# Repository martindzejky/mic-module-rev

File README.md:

# Microphone module reverse-engineered

I had this microphone sensor module lying around. I wanted to understand how it works
so I reverse engineered its schematic. I also ended up re-creating the PCB and a 3D model.

Everything was done in [KiCad](https://www.kicad-pcb.org).

## Images

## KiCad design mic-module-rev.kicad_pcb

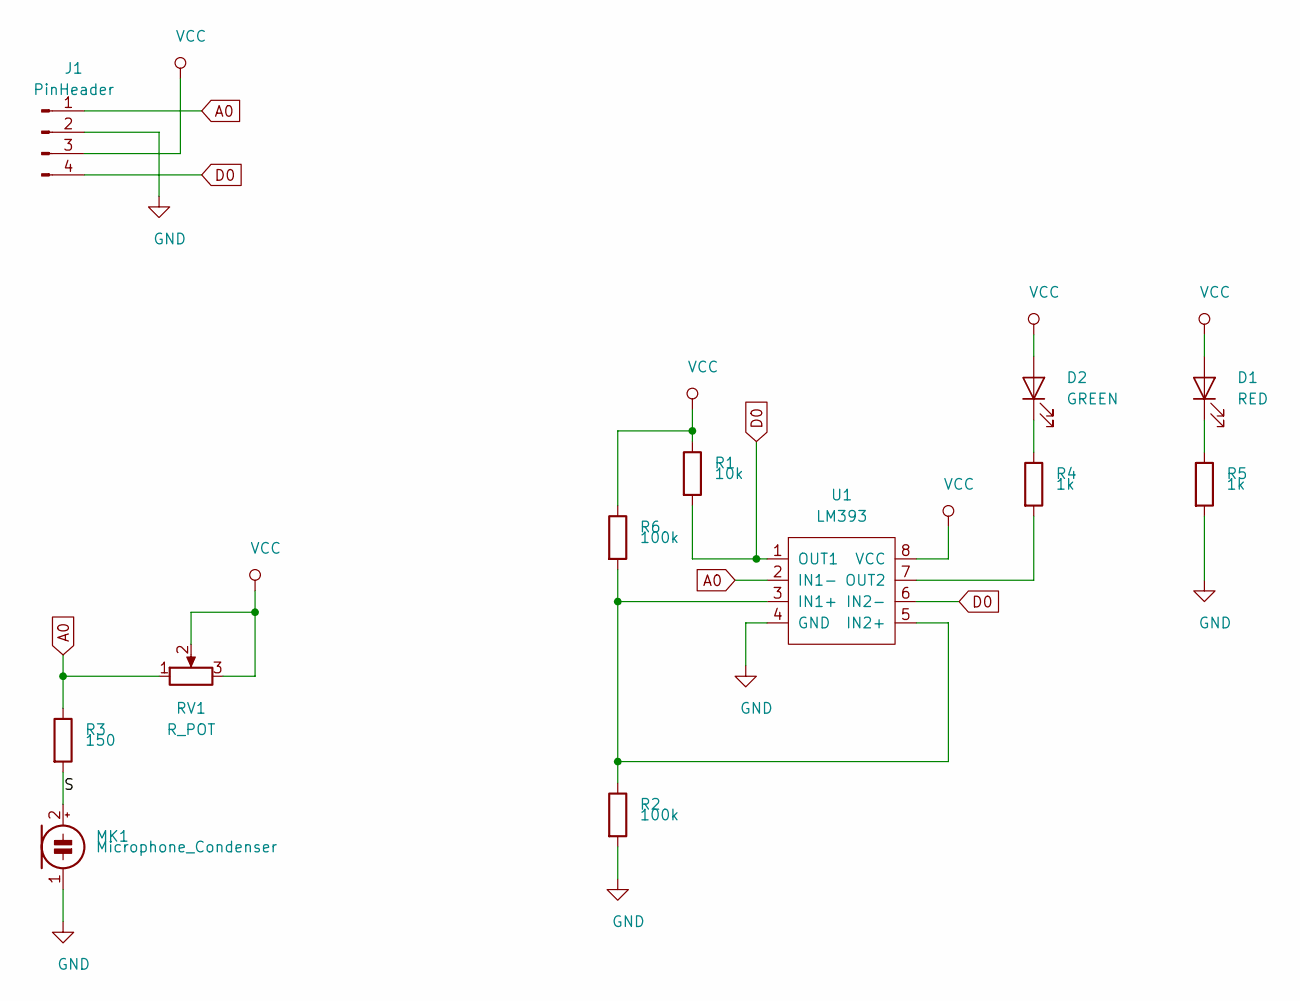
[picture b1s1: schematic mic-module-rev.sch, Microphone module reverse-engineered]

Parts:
D1: RED; LED_0603_1608Metric
D2: GREEN; LED_0603_1608Metric
J1: PinHeader; PinHeader_1x04_P2.00mm_Horizontal
MK1: Microphone_Condenser; C_Disc_D3.4mm_W2.1mm_P2.50mm
R1: 10k; R_0603_1608Metric
R2, R6: 100k; R_0603_1608Metric
R3: 150; R_0603_1608Metric
R4, R5: 1k; R_0603_1608Metric
RV1: R_POT; Potentiometer_Bourns_3296W_Vertical
U1: LM393; SOIC-8_3.9x4.9mm_P1.27mm

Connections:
/S: MK1.2 (+), R3.2
A0: J1.1, R3.1, RV1.1, U1.2 (IN1-)
D0: J1.4, R1.2, U1.1 (OUT1), U1.6 (IN2-)
GND: J1.2, MK1.1 (-), R2.2, R5.2, U1.4 (GND)
unnamed: D1.1 (K), R5.1
unnamed: D2.1 (K), R4.1
unnamed: R2.1, R6.2, U1.3 (IN1+), U1.5 (IN2+)
unnamed: R4.2, U1.7 (OUT2)
VCC: D1.2 (A), D2.2 (A), J1.3, R1.1, R6.1, RV1.2, RV1.3, U1.8 (VCC)

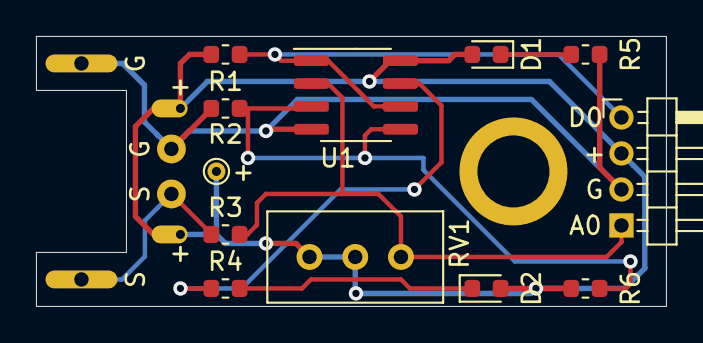
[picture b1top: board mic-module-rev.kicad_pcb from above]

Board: 2 copper layers, 35.0 x 15.0 mm, 12 parts (0 on the bottom side), 9 nets.

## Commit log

2020-04-09 add kicad project files
2020-04-09 create LICENSE
2020-04-09 add images
2020-04-09 write the README
